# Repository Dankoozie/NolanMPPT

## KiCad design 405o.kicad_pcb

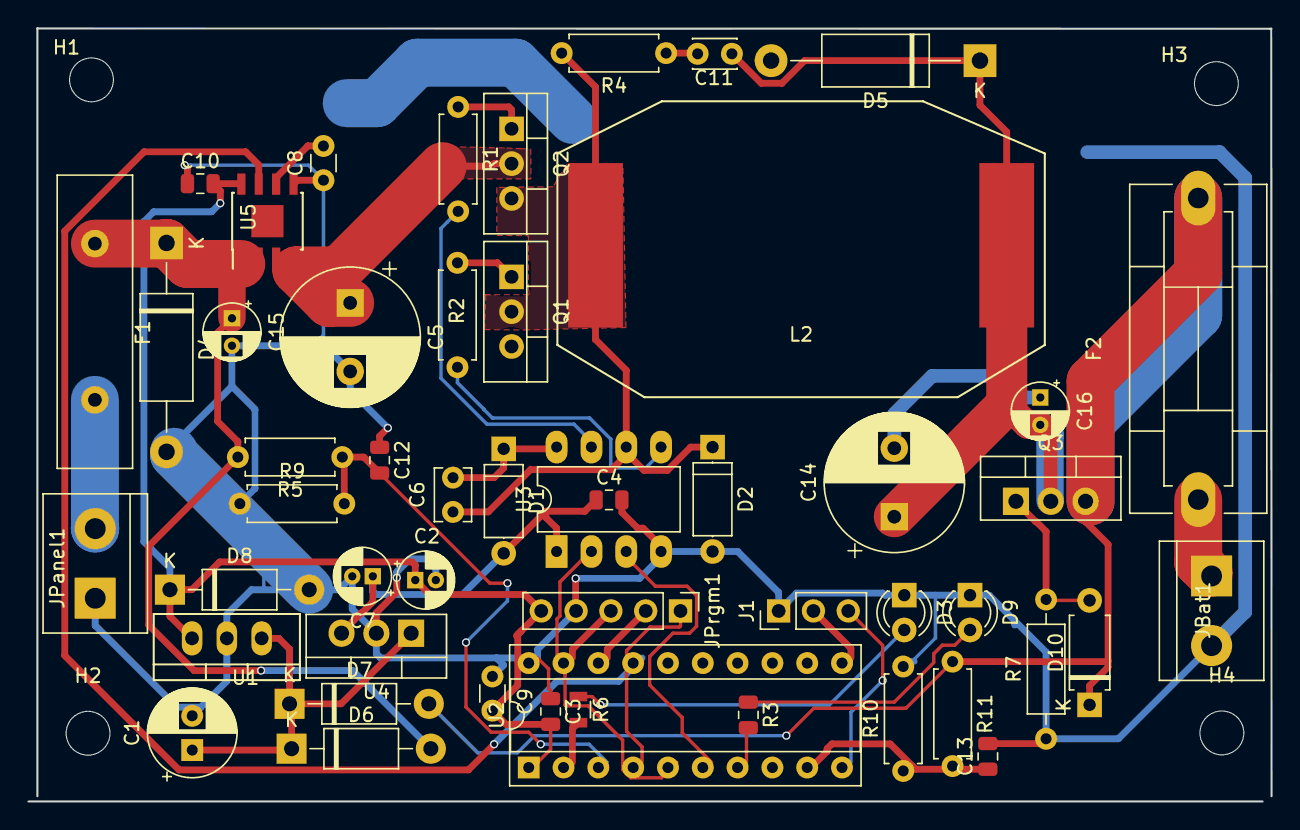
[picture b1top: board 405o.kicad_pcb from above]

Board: 2 copper layers, 90.7 x 56.4 mm, 55 parts (0 on the bottom side), 33 nets.

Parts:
C1: CP; CP_Radial_D6.3mm_P2.50mm
C2, C7: CP; CP_Radial_D4.0mm_P1.50mm
C3, C4, C12, C13: C; C_0805_2012Metric
C5: CP; CP_Radial_D10.0mm_P5.00mm
C6: C; C_Disc_D3.8mm_W2.6mm_P2.50mm
C8: Capacitor_SMD:C_0805_2012Metric; C_Disc_D3.0mm_W1.6mm_P2.50mm
C9: C; C_Disc_D3.0mm_W1.6mm_P2.50mm
C10: 0.11uF; C_0805_2012Metric
C11: C; C_Disc_D3.0mm_W2.0mm_P2.50mm
C14: 1000uF; CP_Radial_D10.0mm_P5.00mm
C15, C16: 10uF; CP_Radial_D4.0mm_P2.00mm
D1: D1; D_A-405_P7.62mm_Horizontal
D2: UF4007; D_A-405_P7.62mm_Horizontal
D3, D9: LED; LED_D3.0mm
D4, D5: D_TVS; D_DO-15_P15.24mm_Horizontal
D6, D7: 1N4001; D_DO-41_SOD81_P10.16mm_Horizontal
D8: 1N4007; D_DO-41_SOD81_P10.16mm_Horizontal
D10: D_Zener; D_A-405_P7.62mm_Horizontal
F1: Fuse; Fuse_Littelfuse-LVR125
F2: Fuse; Fuseholder5x20_horiz_SemiClosed_Casing10x25mm
H1, H2, H3, H4: MountingHole; MountingHole_3.2mm_M3
J1: Conn_01x03; PinHeader_1x03_P2.54mm_Vertical
JBat1: Screw_Terminal_01x02; TerminalBlock_bornier-2_P5.08mm
JPanel1: Screw_Terminal_01x02; TerminalBlock_bornier-2_P5.08mm
JPrgm1: Conn_01x05; PinHeader_1x05_P2.54mm_Vertical
L2: L; pm2120
Q1, Q2: IRF540N; TO-220_Vertical
Q3: Q_PMOS_GDS; TO-220-3_Vertical
R1, R2: 20; R_Axial_DIN0207_L6.3mm_D2.5mm_P7.62mm_Horizontal
R3: 2000; R_0805_2012Metric
R4: 200; R_Axial_DIN0207_L6.3mm_D2.5mm_P7.62mm_Horizontal
R5, R10: 100k; R_Axial_DIN0207_L6.3mm_D2.5mm_P7.62mm_Horizontal
R6: 2000; R_0805
R7: R; R_Axial_DIN0207_L6.3mm_D2.5mm_P10.16mm_Horizontal
R9, R11: 20k; R_Axial_DIN0207_L6.3mm_D2.5mm_P7.62mm_Horizontal
U1: L7805; TO-220_Neutral123_Vertical
U2: 16F1508; DIP-20_W7.62mm_Socket
U3: IR2104; DIP-8_W7.62mm_LongPads
U4: L7812; TO-220-3_Vertical
U5: ACS713xLCTR-05B; SOIC-8-1EP_3.9x4.9mm_Pitch1.27mm

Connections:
+5V: C2.1, C3.2, C9.2, C10.2, D8.1, JPrgm1.5, U1.3, U2.1, U5.8
+12V: C4.1, C7.1, D1.2, U3.1, U4.3
CSense: U2.17, U5.7
GND: C1.2, C2.2, C3.1, C4.2, C5.2, C7.2, C8.1, C9.1, C10.1, C12.1, C13.2, C14.2, C15.2, C16.1, D2.2, D3.1, D4.2, D5.2, D8.2, D9.1, J1.1, JBat1.2, JPanel1.1, JPrgm1.4, Q1.3, R7.1, R9.1, R10.2, U1.2, U2.20, U3.4, U4.2, U5.5
IN-: C5.1, Q2.2, U5.3, U5.4
Mickler: JPrgm1.1, U2.4
unnamed: C1.1, D6.1, D7.1, U1.1, U4.1
unnamed: C6.1, D2.1, L2.1, Q1.2, Q2.3, R4.2, U3.6
unnamed: C6.2, D1.1, U3.8
unnamed: C8.2, U5.6
unnamed: C11.1, C14.1, C16.2, D5.1, L2.2, Q3.2
unnamed: C11.2, R4.1
unnamed: C15.1, D4.1, D6.2, F1.1, R5.2, U5.1, U5.2
unnamed: D3.2, R6.1
unnamed: D9.2, R3.1
unnamed: D10.2, Q3.1, R7.2
unnamed: F1.2, JPanel1.2
unnamed: F2.1, JBat1.1
unnamed: J1.2, U2.11
unnamed: J1.3, U2.10
unnamed: JPrgm1.2, U2.18
unnamed: JPrgm1.3, U2.19
unnamed: Q1.1, R2.1
unnamed: Q2.1, R1.1
unnamed: R1.2, U3.7
unnamed: R2.2, U3.5
unnamed: R3.2, U2.7
unnamed: R6.2, U2.2
unnamed: U2.5, U3.2
unnamed: U2.6, U3.3
VB: D7.2, D10.1, F2.2, Q3.3, R11.1
VB_Sense: C13.1, R10.1, R11.2, U2.9
VP_Sense: C12.2, R5.1, R9.2, U2.3

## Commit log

2019-08-31 Schematic and kicad project added
    This is a MPPT controller based on the famous Tim Nolan design, but uses a PIC16F instead of arduino
